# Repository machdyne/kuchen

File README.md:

# Kuchen Computer

Kuchen is an FPGA computer designed by Lone Dynamics Corporation.

This repo contains PCB layouts, schematics, pinouts, example gateware and documentation.

Find more information on the [Kuchen product page](https://machdyne.com/product/kuchen-computer/).

## Blinky 

Building the blinky example requires [Yosys](https://github.com/YosysHQ/yosys), [nextpnr-ice40](https://github.com/YosysHQ/nextpnr) and [IceStorm](https://github.com/YosysHQ/icestorm).

Assuming they are installed, you can simply type `make` to build the gateware, which will be written to output/blinky.bin. You can then use [ldprog](https://github.com/machdyne/ldprog) to write the gateware to the device over the ISP header, or use the USB DFU bootloader:

```
$ dfu-util -a 0 -D output/blinky.bin
```

Exit the bootloader and continue booting:

```
sudo dfu-util -e -a 0
```

## Zucker

[Zucker](https://github.com/machdyne/zucker) is a RISC-V SOC that supports Kuchen.

## USB Bootloader

Kuchen supports updating the flash MMOD over its USB-C port with the USB DFU (Device Firmware Upgrade) protocol. When Kuchen powers on (or restarts) the USB bootloader waits 5 seconds for a USB command and then continues the boot process, if it receives a command it will wait until the device is detached (with `dfu-util -e`) or rebooted (with `ldprog -r`).

Kuchen ships with the DFU bootloader on the MMOD. In order to re-install the USB bootloader you will need to use the ISP header and [ldprog](https://github.com/machdyne/ldprog). Make sure you have first installed the software required to build the Blinky example above.

```
git clone https://github.com/machdyne/tinydfu-bootloader
cd tinydfu-bootloader/boards/kuchen
make
make prog
```

Now you can program the flash MMOD over USB:

```
ldprog -r
sudo dfu-util -a 0 -D zucker/output/kuchen/soc.bin
sudo dfu-util -a 1 -D zucker/apps/lix/lix.bin
```

Exit the bootloader and continue booting:

```
sudo dfu-util -e -a 0
```

## ISP Header

The ISP header can be used to program the FPGA SRAM as well as the MMOD flash memory. 

```
7 5 3 1
8 6 4 2
```

| Pin | Signal |
| --- | ------ |
| 1 | CSPI\_SS |
| 2 | CSPI\_SCK |
| 3 | CSPI\_SI |
| 4 | CSPI\_SO |
| 5 | CRESET |
| 6 | CDONE |
| 7 | GND |
| 8 | PWR5V0 |

## Board Revisions

| Revision | Notes |
| -------- | ----- |
| V0 | Initial production boards |
| V1 | Move DQ7 from K14 to J14 |

## License

The contents of this repo are released under the [Lone Dynamics Open License](LICENSE.md).

Note: You can use these designs for commercial purposes but we ask that instead of producing exact clones, that you either replace our trademarks and logos with your own or add your own next to ours.

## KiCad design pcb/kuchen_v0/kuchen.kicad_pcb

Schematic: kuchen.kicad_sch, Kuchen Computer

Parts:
C1, C4, C7, C9, C10, C12, C14, C15, C21, C31, C32, C33, C34, C35, C36, C39: 100nF; C_0603_1608Metric
C2, C3, C5, C6: 1uF; C_0603_1608Metric
C11, C22, C23: 220nF; C_0603_1608Metric
C13, C30: 4.7uF; R_0603_1608Metric
C17, C18, C37, C38, C48: 10uF; C_0603_1608Metric
C26, C28, C29: 10nF; C_0603_1608Metric
C40: 10uF; R_0603_1608Metric
C41: 100nF; R_0603_1608Metric
C42, C43: 4.7uF; C_0603_1608Metric
C44, C45: 10pF; C_0603_1608Metric
C46, C47, C49: 22uF; C_0603_1608Metric
D1: D_Schottky_Small; D_0603_1608Metric
D2: LED; LED_0603_1608Metric
FB1, FB2: Ferrite_Bead; R_0603_1608Metric
H1, H2, H3, H4: MountingHole_Pad; MountingHole_3.2mm_M3_Pad
J1: TYPE-C-31-M-12-FIXED; USB_C_Receptacle_HRO_TYPE-C-31-M-12-BIG-PADS; PARTREV A
J2: USB_A; USB_A_Stewart_SS-52100-001_Horizontal
J3: MICROSD; TF-018B-H15
J4: HDMI_A; HDMI_TE_1827059-3-FIXED
L1, L2: INDUCTOR; L_0805_2012Metric
MMOD1: PMOD-Device-x1-Type-2-SPI; PinSocket_1x06_P2.54mm_Horizontal
PMOD1, PMOD2: PMOD-Device-x2-Type-1A-GPIO; PMOD_2x06_HOST
PROG1: Conn_02x04_Top_Bottom; PinHeader_2x04_P2.54mm_Vertical
R1, R7: 5K1; R_0603_1608Metric
R2, R3, R11, R12: 22R; R_0603_1608Metric
R4, R5, R6, R8: 10K; R_0603_1608Metric
R9, R10: 100R; R_0603_1608Metric
R13: 536R; R_0603_1608Metric
R14, R16, R18, R19: 20K; R_0603_1608Metric
R22, R23, R24, R25, R26, R27, R28, R29: 270R; R_0402_1005Metric
R30, R37: 1K5; R_0603_1608Metric
R31, R32: 120K; R_0603_1608Metric
R33: 210K; R_0603_1608Metric
R34: 47K; R_0603_1608Metric
R35, R36: 15K; R_0603_1608Metric
TP1: TP_PWR5V0; TestPoint_THTPad_D1.0mm_Drill0.5mm
TP2: TP_PWR1V2; TestPoint_THTPad_D1.0mm_Drill0.5mm
TP3: TP_PWR3V3; TestPoint_THTPad_D1.0mm_Drill0.5mm
U1: ICE40HX8K-CT256; BGA256C80P16X16_1400X1400X170; PART_REV 3.4
U2: W9825G6KH-6; SOP80P1176X120-54N; PARTREV A05
U3, U4: TLV62568DDC; SOT-23-6
Y1: KC2016Z48.0000C1KX00; OSC_KC2016Z13.5600C1KX00; PARTREV November 2020

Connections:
/CDONE: PROG1.6, R6.1, U1.M10 (CDONE)
/CK_N: J4.12 (CK-), R29.2
/CK_P: J4.10 (CK+), R28.2
/CLK48: U1.F7 (IOT_198_GBIN0), Y1.3 (OUTPUT)
/CRESET: PROG1.5, R8.1, U1.N11 (CRESET_B)
/CSPI_SCK: MMOD1.3 (MISO), PROG1.2, R5.1, U1.R11 (IOB_107_SCK)
/CSPI_SI: MMOD1.4 (SCK), PROG1.3, U1.P11 (IOB_106_SDI)
/CSPI_SO: MMOD1.5 (GND), PROG1.4, U1.P12 (IOB_105_SDO)
/CSPI_SS: MMOD1.6 (VCC), PROG1.1, R4.1, U1.R12 (IOB_108_SS)
/D0_N: J4.9 (D0-), R27.2
/D0_P: J4.7 (D0+), R26.2
/D1_N: J4.6 (D1-), R25.2
/D1_P: J4.4 (D1+), R24.2
/D2_N: J4.3 (D2-), R23.2
/D2_P: J4.1 (D2+), R22.2
/DRAM_A0: U1.L13 (IOR_118), U2.23 (A0)
/DRAM_A1: U1.L12 (IOR_116), U2.24 (A1)
/DRAM_A2: U1.K12 (IOR_120), U2.25 (A2)
/DRAM_A3: U1.J11 (IOR_126), U2.26 (A3)
/DRAM_A4: U1.H13 (IOR_139), U2.29 (A4)
/DRAM_A5: U1.H14 (IOR_142), U2.30 (A5)
/DRAM_A6: U1.G13 (IOR_152), U2.31 (A6)
/DRAM_A7: U1.F13 (IOR_162), U2.32 (A7)
/DRAM_A8: U1.F14 (IOR_155), U2.33 (A8)
/DRAM_A9: U1.E13 (IOR_166), U2.34 (A9)
/DRAM_A10: U1.M13 (IOR_114), U2.22 (A10/AP)
/DRAM_A11: U1.E14 (IOR_160), U2.35 (A11)
/DRAM_A12: U1.F12 (IOR_156), U2.36 (A12)
/DRAM_BS0: U1.M11 (IOB_93), U2.20 (BS0)
/DRAM_BS1: U1.N12 (IOB_98), U2.21 (BS1)
/DRAM_CAS: U1.K15 (IOR_131), U2.17 (~CAS)
/DRAM_CKE: U1.D14 (IOR_167), U2.37 (CKE)
/DRAM_CLK: U1.J15 (IOR_130), U2.38 (CLK)
/DRAM_CS: U1.M14 (IOR_115), U2.19 (~CS)
/DRAM_DQ0: U1.R15 (IOR_110), U2.2 (DQ0)
/DRAM_DQ1: U1.P15 (IOR_112), U2.4 (DQ1)
/DRAM_DQ2: U1.P16 (IOR_113), U2.5 (DQ2)
/DRAM_DQ3: U1.N16 (IOR_117), U2.7 (DQ3)
/DRAM_DQ4: U1.M15 (IOR_123), U2.8 (DQ4)
/DRAM_DQ5: U1.M16 (IOR_121), U2.10 (DQ5)
/DRAM_DQ6: U1.L16 (IOR_127), U2.11 (DQ6)
/DRAM_DQ7: U1.K14 (IOR_129), U2.13 (DQ7)
/DRAM_DQ8: U1.G15 (IOR_145), U2.42 (DQ8)
/DRAM_DQ9: U1.F16 (IOR_147), U2.44 (DQ9)
/DRAM_DQ10: U1.F15 (IOR_149), U2.45 (DQ10)
/DRAM_DQ11: U1.E16 (IOR_151), U2.47 (DQ11)
/DRAM_DQ12: U1.D16 (IOR_153), U2.48 (DQ12)
/DRAM_DQ13: U1.D15 (IOR_157), U2.50 (DQ13)
/DRAM_DQ14: U1.C16 (IOR_161), U2.51 (DQ14)
/DRAM_DQ15: U1.B16 (IOR_165), U2.53 (DQ15)
/DRAM_LDQM: U1.K16 (IOR_133), U2.15 (LDQM)
/DRAM_RAS: U1.J16 (IOR_138), U2.18 (~RAS)
/DRAM_UDQM: U1.G16 (IOR_143), U2.39 (UDQM)
/DRAM_WE: U1.L14 (IOR_119), U2.16 (~WE)
/DVI_CK_N: R29.1, U1.T8 (IOB_76)
/DVI_CK_P: R28.1, U1.T9 (IOB_79)
/DVI_D0_N: R27.1, U1.T10 (IOB_88)
/DVI_D0_P: R26.1, U1.T11 (IOB_89)
/DVI_D1_N: R25.1, U1.T13 (IOB_94)
/DVI_D1_P: R24.1, U1.T14 (IOB_92)
/DVI_D2_N: R23.1, U1.T15 (IOB_91)
/DVI_D2_P: R22.1, U1.T16 (IOB_100)
/LED: R13.2, U1.C13 (IOT_174)
/LEDC: D2.1 (K), R13.1
/PMOD_A1: PMOD1.1 (IOA0), U1.F5 (IOL_2A)
/PMOD_A2: PMOD1.2 (IOA1), U1.E4 (IOL_1A)
/PMOD_A3: PMOD1.3 (IOA2), U1.E2 (IOL_7B)
/PMOD_A4: PMOD1.4 (IOA3), U1.B2 (IOL_1B)
/PMOD_A7: PMOD1.7 (IOB0), U1.F4 (IOL_4A)
/PMOD_A8: PMOD1.8 (IOB1), U1.E3 (IOL_6B)
/PMOD_A9: PMOD1.9 (IOB2), U1.C1 (IOL_3A)
/PMOD_A10: PMOD1.10 (IOB3), U1.B1 (IOL_2B)
/PMOD_B1: PMOD2.1 (IOA0), U1.B13 (IOT_178)
/PMOD_B2: PMOD2.2 (IOA1), U1.C11 (IOT_180)
/PMOD_B3: PMOD2.3 (IOA2), U1.D11 (IOT_181)
/PMOD_B4: PMOD2.4 (IOA3), U1.B15 (IOT_169)
/PMOD_B7: PMOD2.7 (IOB0), U1.B11 (IOT_184)
/PMOD_B8: PMOD2.8 (IOB1), U1.B12 (IOT_182)
/PMOD_B9: PMOD2.9 (IOB2), U1.A15 (IOT_177)
/PMOD_B10: PMOD2.10 (IOB3), U1.A16 (IOT_176)
/PWR1V2: C3.1, C6.1, C11.1, C22.1, C23.1, C26.1, C28.1, C29.1, C44.1, C46.1, C47.1, L1.2, R9.1, R10.1, R31.1, TP2.1, U1.A14 (VCC), U1.F6 (VCC), U1.F10 (VCC), U1.K6 (VCC), U1.K10 (VCC), U1.L2 (VCC)
/PWR2V5: C10.1, D1.1 (K), U1.E12 (VPP_2V5)
/PWR3V3: C1.1, C2.1, C4.1, C5.1, C7.1, C9.1, C12.1, C21.1, C31.2, C32.2, C33.2, C34.2, C35.2, C36.2, C37.2, C38.2, C39.1, C40.1, C41.1, C45.1, C48.1, C49.1, D1.2 (A), D2.2 (A), J3.4 (VDD), L2.2, MMOD1.1 (SS), PMOD1.6 (VCC), PMOD1.12 (VCC), PMOD2.6 (VCC), PMOD2.12 (VCC), R4.2, R5.2, R6.2, R8.2, R14.1, R16.1, R18.1, R19.1, R33.1, TP3.1, U1.A3 (VCCIO_0), U1.A8 (VCCIO_0), U1.A13 (VCCIO_0), U1.C15 (VCCIO_1), U1.E1 (VCCIO_3), U1.F8 (VCCIO_0), U1.G6 (VCCIO_3), U1.H10 (VCCIO_1), U1.H15 (VCCIO_1), U1.J6 (VCCIO_3), U1.K8 (VCCIO_2), U1.N1 (VCCIO_3), U1.N13 (VCC_SPI), U1.N15 (VCCIO_1), U1.P3 (VCCIO_2), U1.R8 (VCCIO_2), U1.R13 (VCCIO_2), U2.1 (VDD), U2.3 (VDDQ), U2.9 (VDDQ), U2.14 (VDD), U2.27 (VDD), U2.43 (VDDQ), U2.49 (VDDQ), Y1.1 (INH), Y1.4 (VCC)
/PWR3V3EN: R30.2, U3.5 (PG), U4.1 (EN)
/PWR5V0: C13.1, C30.1, C42.1, C43.1, FB1.1, FB2.1, J4.18 (+5V), PROG1.8, R30.1, TP1.1, U3.1 (EN), U3.4 (VIN), U4.4 (VIN)
/SD_MISO: J3.7 (DAT0), R14.2, U1.A2 (IOT_218)
/SD_MOSI: J3.3 (CMD), R18.2, U1.C4 (IOT_222)
/SD_SCK: J3.5 (CLK), R16.2, U1.A1 (IOT_220)
/SD_SS: J3.2 (DAT3/CD), R19.2, U1.C5 (IOT_221)
/USBH_CONN_DN: J2.2 (D-), R12.2, R36.1
/USBH_CONN_DP: J2.3 (D+), R11.2, R35.1
/USBH_DN: R12.1, U1.H1 (IOL_14B)
/USBH_DP: R11.1, U1.J1 (IOL_15B)
/USB_CONN_DN: J1.A7 (DN1), J1.B7 (DN2), R2.1
/USB_CONN_DP: J1.A6 (DP1), J1.B6 (DP2), R3.1, R37.1
/USB_DN: R2.2, U1.T1 (IOB_53)
/USB_DP: R3.2, U1.T2 (IOB_57)
/USB_DP_PU: R37.2, U1.T3 (IOB_61)
GND: C1.2, C2.2, C3.2, C4.2, C5.2, C6.2, C7.2, C9.2, C10.2, C11.2, C12.2, C13.2, C21.2, C22.2, C23.2, C26.2, C28.2, C29.2, C30.2, C31.1, C32.1, C33.1, C34.1, C35.1, C36.1, C37.1, C38.1, C39.2, C40.2, C41.2, C42.2, C43.2, C46.2, C47.2, C48.2, C49.2, H1.1, H2.1, H3.1, H4.1, J1.A1 (GND), J1.A12 (GND), J1.B1 (GND), J1.B12 (GND), J1.S1 (SHIELD), J1.S2 (SHIELD), J1.S3 (SHIELD), J1.S4 (SHIELD), J2.4 (GND), J2.5 (Shield), J3.6 (VSS), J4.2 (D2S), J4.5 (D1S), J4.8 (D0S), J4.11 (CKS), J4.17 (GND), J4.S1 (SH), J4.S2 (SH), J4.S3 (SH), J4.S4 (SH), MMOD1.2 (MOSI), PMOD1.5 (GND), PMOD1.11 (GND), PMOD2.5 (GND), PMOD2.11 (GND), PROG1.7, R1.2, R7.2, R32.2, R34.2, R35.2, R36.2, U1.A4 (GND), U1.A12 (GND), U1.E15 (GND), U1.G7 (GND), U1.G8 (GND), U1.G9 (GND), U1.H7 (GND), U1.H8 (GND), U1.H9 (GND), U1.J7 (GND), U1.J8 (GND), U1.J9 (GND), U1.K2 (GND), U1.K7 (GND), U1.L15 (GND), U1.R7 (GND), U1.T4 (GND), U1.T12 (GND), U2.6 (VSSQ), U2.12 (VSSQ), U2.28 (VSS), U2.41 (VSS), U2.46 (VSSQ), U2.52 (VSSQ), U2.54 (VSS), U3.2 (GND), U4.2 (GND), Y1.2 (CASE_GND)
unnamed: C14.1, C17.1, R9.2, U1.L8 (VCCPLL0)
unnamed: C14.2, C17.2, U1.N8 (GNDPLL0)
unnamed: C15.1, C18.1, R10.2, U1.E8 (VCCPLL1)
unnamed: C15.2, C18.2, U1.E7 (GNDPLL1)
unnamed: C44.2, R31.2, R32.1, U3.6 (FB)
unnamed: C45.2, R33.2, R34.1, U4.6 (FB)
unnamed: FB1.2, J1.A4 (VBUS), J1.A9 (VBUS), J1.B4 (VBUS), J1.B9 (VBUS)
unnamed: FB2.2, J2.1 (VBUS)
unnamed: J1.A5 (CC1), R1.1
unnamed: J1.B5 (CC2), R7.1
unnamed: L1.1, U3.3 (SW)
unnamed: L2.1, U4.3 (SW)

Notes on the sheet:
0.6V * (1 + (120/120)) = 1.2V
3V3
KUCHEN
0.6V * (1 + (210/47)) = 3.28V
USB HOST
USB POWER & DEVICE

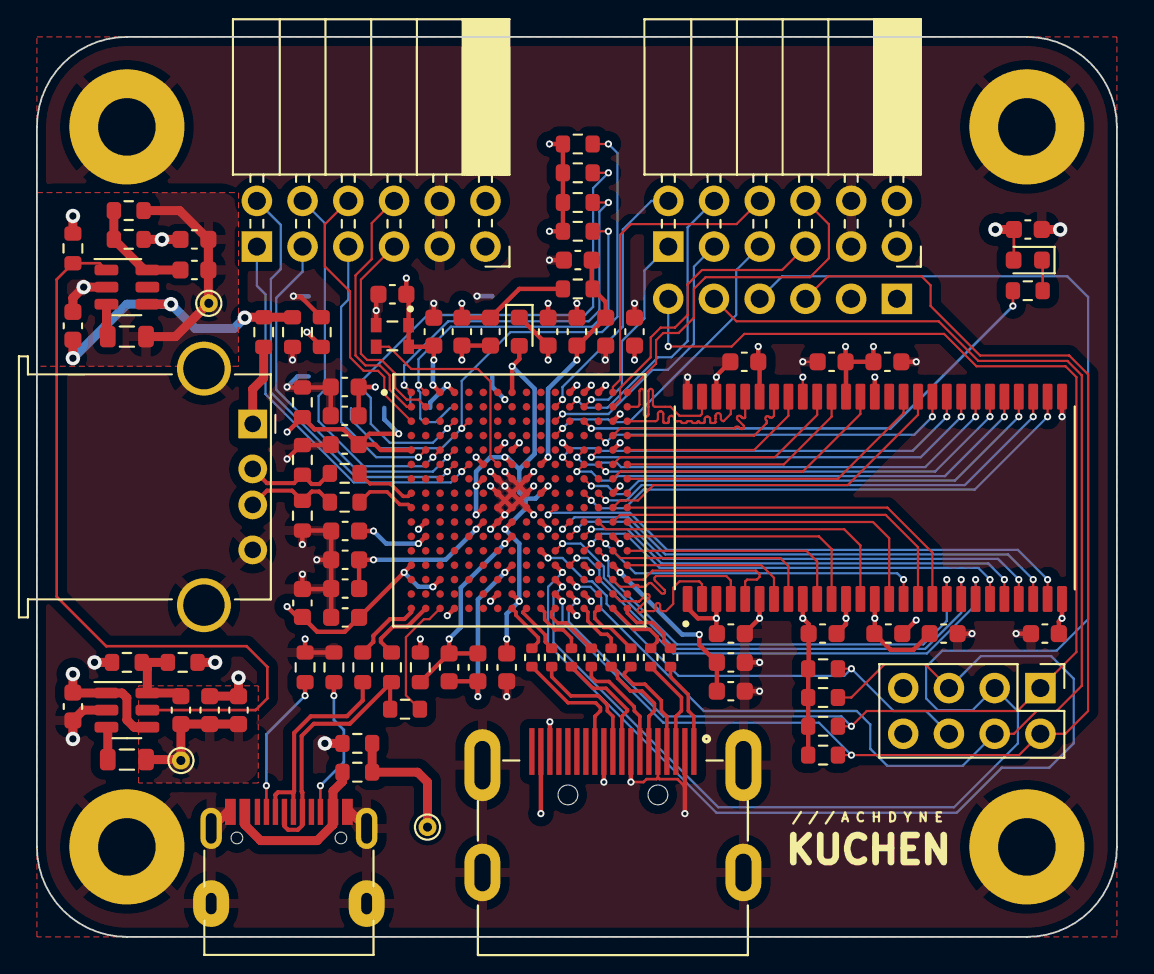
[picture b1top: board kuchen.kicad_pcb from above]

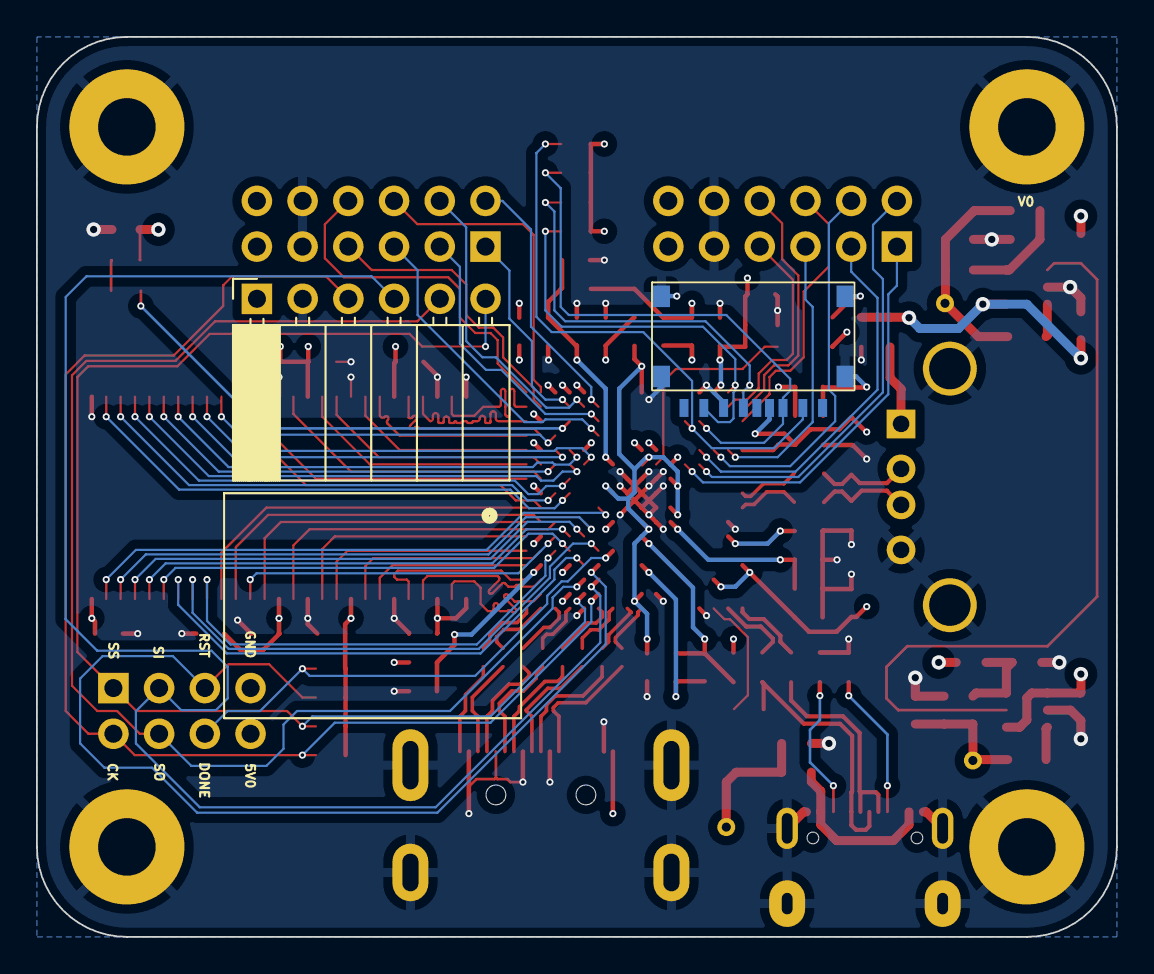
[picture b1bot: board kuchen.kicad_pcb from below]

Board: 4 copper layers, 60.0 x 50.0 mm, 101 parts (2 on the bottom side), 111 nets.

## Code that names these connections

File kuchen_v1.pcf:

# Kuchen V0
# ---------

set_io CLK_48		F7

set_io LED			C13

# PMOD A
set_io PMOD_A1		F5
set_io PMOD_A2		E4
set_io PMOD_A3		E2
set_io PMOD_A4		B2
set_io PMOD_A7		F4
set_io PMOD_A8		E3
set_io PMOD_A9		C1
set_io PMOD_A10	B1

# PMODB
set_io PMOD_B1		B13
set_io PMOD_B2		C11
set_io PMOD_B3		D11
set_io PMOD_B4		B15
set_io PMOD_B7		B11
set_io PMOD_B8		B12
set_io PMOD_B9		A15
set_io PMOD_B10	A16

# USB-UART on PMODB
set_io UART0_RTS  B13
set_io UART0_RX   C11
set_io UART0_TX   D11
set_io UART0_CTS  B15

# SDRAM
set_io sdram_dq[0]	R15
set_io sdram_dq[1]	P15
set_io sdram_dq[2]	P16
set_io sdram_dq[3]	N16
set_io sdram_dq[4]	M15
set_io sdram_dq[5]	M16
set_io sdram_dq[6]	L16
set_io sdram_dq[7]	J14
set_io sdram_dq[8]	G15
set_io sdram_dq[9]	F16
set_io sdram_dq[10]	F15
set_io sdram_dq[11]	E16
set_io sdram_dq[12]	D16
set_io sdram_dq[13]	D15
set_io sdram_dq[14]	C16
set_io sdram_dq[15]	B16
set_io sdram_dm[0]	K16
set_io sdram_dm[1]	G16
set_io sdram_cke	D14
set_io sdram_clock	J15
set_io sdram_cas_n	K15
set_io sdram_ras_n	J16
set_io sdram_cs_n		M14
set_io sdram_we_n		L14
set_io sdram_ba[0]	M11
set_io sdram_ba[1]	N12
set_io sdram_a[0]		L13
set_io sdram_a[1]		L12
set_io sdram_a[2]		K12
set_io sdram_a[3]		J11
set_io sdram_a[4]		H13
set_io sdram_a[5]		H14
set_io sdram_a[6]		G13
set_io sdram_a[7]		F13
set_io sdram_a[8]		F14
set_io sdram_a[9]		E13
set_io sdram_a[10]	M13
set_io sdram_a[11]	E14
set_io sdram_a[12]	F12

# DDMI
set_io DDMI_D0_N	T10
set_io DDMI_D1_N	T13
set_io DDMI_D2_N	T15
set_io DDMI_CK_N	T8
set_io DDMI_D0_P	T11
set_io DDMI_D1_P	T14
set_io DDMI_D2_P	T16
set_io DDMI_CK_P	T9

# MicroSD
set_io SD_SS	C5
set_io SD_MISO	A2
set_io SD_MOSI	C4
set_io SD_SCK	A1

# USB-C DEVICE
set_io USB_DN		T1
set_io USB_DP		T2
set_io USB_DP_PU	T3

# USB-A HOST
set_io USBH_DN		H1
set_io USBH_DP		J1

# CONFIG SPI
set_io SPI_SS		R12
set_io SPI_SCK		R11
set_io SPI_MISO	P11	# CSPI_SI
set_io SPI_MOSI	P12	# CSPI_SO

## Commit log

2023-10-14 add image
2023-10-14 fix pinout
2023-10-14 rotate diagram
2023-10-16 complete pcf
2023-10-16 add case
2023-10-19 add zucker soc image
2023-10-19 add lix image
2023-11-09 add litex images
2023-11-13 add latest zucker image
2023-11-24 add v1 pcf
2023-11-26 add v1 images
2024-06-26 update makefile

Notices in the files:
pcb/kuchen_v0/kuchen.kicad_sch:
Copyright © 2023 Lone Dynamics Corporation
